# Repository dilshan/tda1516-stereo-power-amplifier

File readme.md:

# TDA1516BQ 12W x 2 Stereo Amplifier

A simple stereo amplifier built around the classic Philips TDA1516BQ audio amplifier chip. It delivers 12W per channel on a 12V - 14V supply, with the warm, smooth sound of a traditional class AB design.

## Features

- Stereo output, 12W x 2
- 12V - 14V supply (tested with a 12V 5A PSU)
- Small PCB: 62mm x 41mm

## Bill of Materials

| Reference | Value | Qty |
|-----------|-------|-----|
| C1 | [100µF / 25V](https://s.click.aliexpress.com/e/_c3xrOqJD) | 1 |
| C2, C3 | [0.22µF](https://s.click.aliexpress.com/e/_c39Y1Dd1) | 2 |
| C4, C5 | [1000µF / 25V](https://s.click.aliexpress.com/e/_c3CeWXvv) | 2 |
| C6 | [2200µF / 25V](https://s.click.aliexpress.com/e/_c3xxjTBN) | 1 |
| C7 | [0.1µF](https://s.click.aliexpress.com/e/_c39Y1Dd1) | 1 |
| J1, J2, J3, J4, J5 | [5.08mm 2-pin screw terminal](https://s.click.aliexpress.com/e/_c3N5smMT) | 5 |
| RV1 | [B100K potentiometer](https://s.click.aliexpress.com/e/_c3qUNW6J) | 1 |
| U1 | [TDA1516BQ](https://s.click.aliexpress.com/e/_c3Xf7b8X) ([datasheet](https://pdf.datasheetcatalog.com/datasheet/philips/TDA1516.pdf)) | 1 |

The PCB can be ordered directly from [PCBWay](https://www.pcbway.com/project/shareproject/TDA1516BQ_12W_x_2_Stereo_Amplifier_b292c3b0.html).

## Construction notes

The build is straightforward. The only thing that needs care is mounting the heatsink. Large capacitors leave little room for tightening the heatsink screws, so use one of these approaches:

1. Solder the TDA1516BQ first, attach the heatsink, then solder the remaining components.
2. Solder all passive components and connectors first, and solder the TDA1516BQ last with the heatsink already attached.

## Power

Use a 12V supply, rated 5A or more. The amplifier works well and produces good quality audio with a 12V 5A PSU.

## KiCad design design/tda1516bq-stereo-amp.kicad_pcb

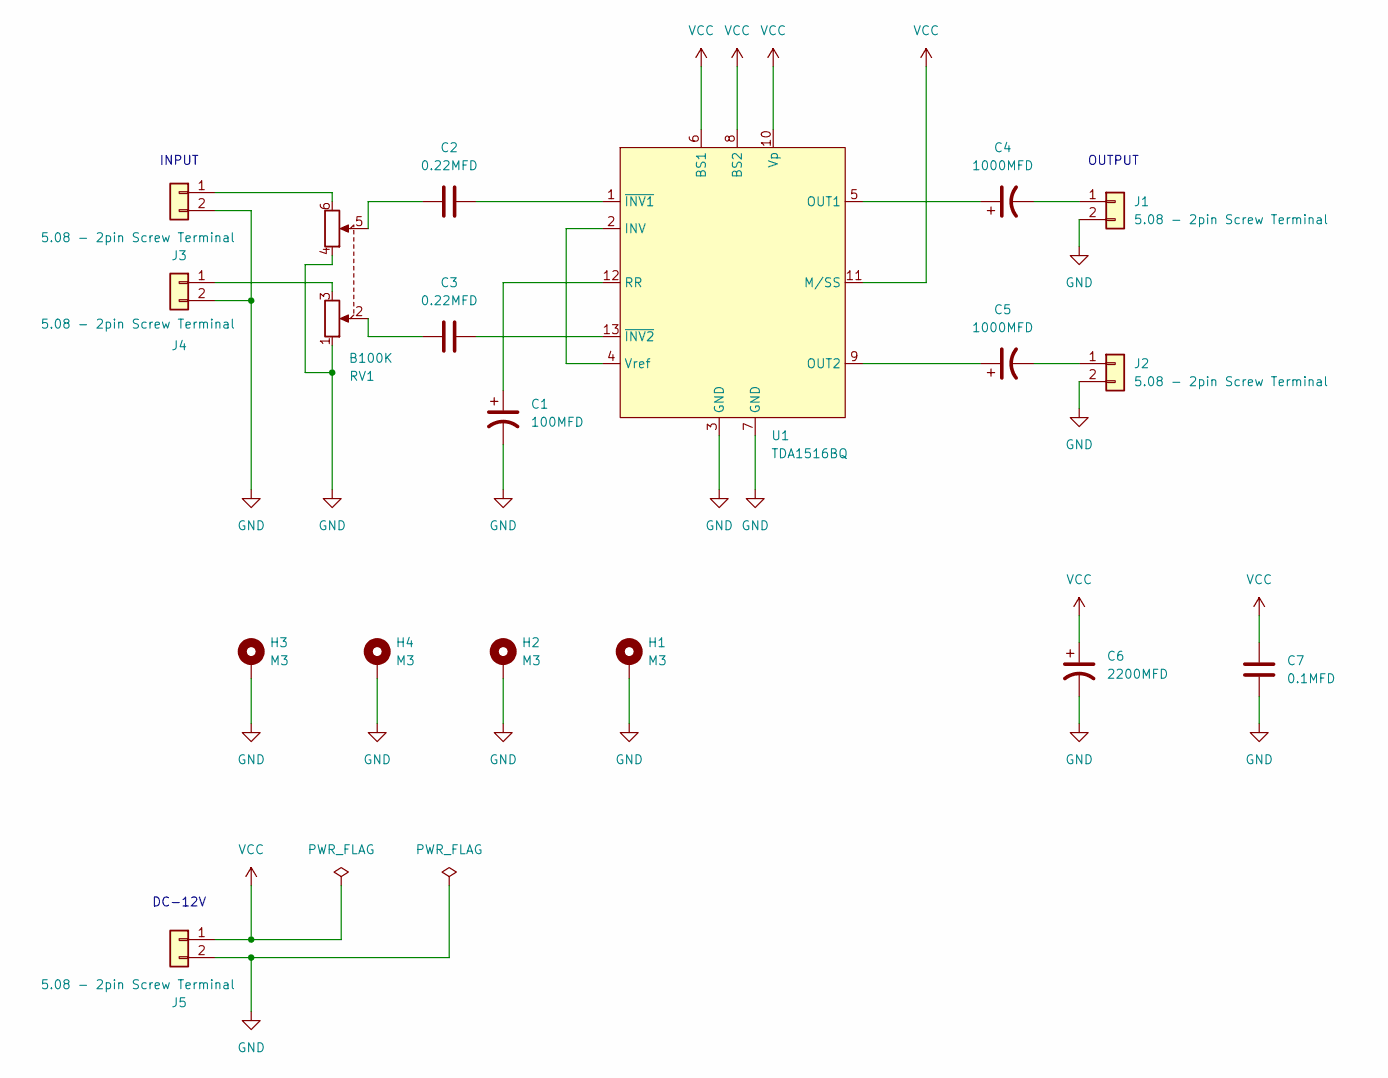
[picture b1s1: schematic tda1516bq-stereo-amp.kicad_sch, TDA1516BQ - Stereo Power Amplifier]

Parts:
C1: 100MFD; CP_Radial_D8.0mm_P3.80mm
C2, C3: 0.22MFD; C_Rect_L11.0mm_W5.1mm_P10.00mm_MKT
C4, C5: 1000MFD; CP_Radial_D12.5mm_P5.00mm
C6: 2200MFD; CP_Radial_D16.0mm_P7.50mm
C7: 0.1MFD; C_Rect_L9.0mm_W4.2mm_P7.50mm_MKT
H1, H2, H3, H4: M3; MountingHole_3.2mm_M3_DIN965_Pad
J1, J2, J3, J4, J5: 5.08 - 2pin Screw Terminal; PhoenixContact_MCV_1,5_2-G-5.08_1x02_P5.08mm_Vertical
RV1: B100K; Potentiometer_Dual
U1: TDA1516BQ; MULTIWAT-SIL13

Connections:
GND: C1.2, C6.2, C7.1, H1.1, H2.1, H3.1, H4.1, J1.2, J2.2, J3.2, J4.2, J5.2, RV1.1, RV1.4, U1.3 (GND), U1.7 (GND)
unnamed: C2.1, RV1.5
unnamed: C3.1, RV1.2
unnamed: C4.2, J1.1
unnamed: C5.2, J2.1
unnamed: J3.1, RV1.6
unnamed: J4.1, RV1.3
unnamed: U1.2 (INV), U1.4 (Vref)
unnamed: C4.1, U1.5 (OUT1)
unnamed: C5.1, U1.9 (OUT2)
unnamed: C1.1, U1.12 (RR)
unnamed: C2.2, U1.1 (~INV1)
unnamed: C3.2, U1.13 (~INV2)
VCC: C6.1, C7.2, J5.1, U1.6 (BS1), U1.8 (BS2), U1.10 (Vp), U1.11 (M/SS)

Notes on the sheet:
INPUT
DC-12V
OUTPUT

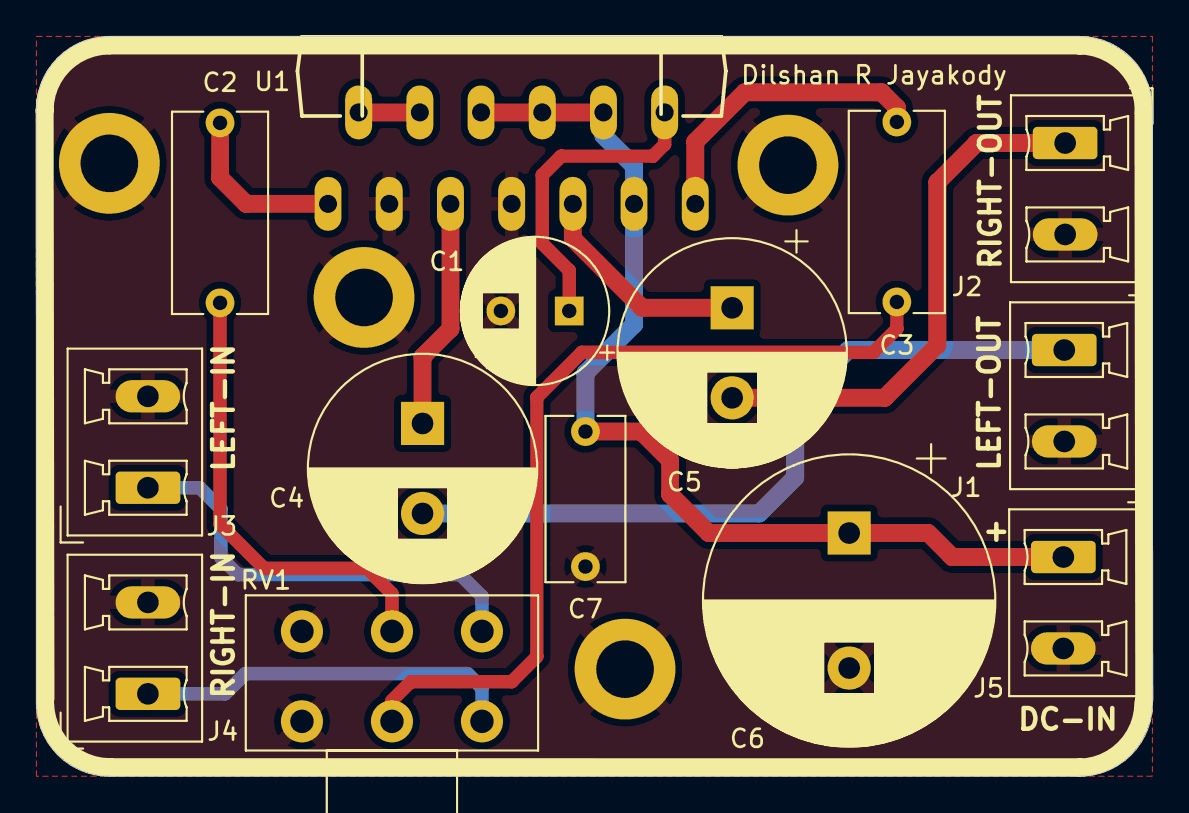
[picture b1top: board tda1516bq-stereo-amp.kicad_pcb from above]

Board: 2 copper layers, 62.0 x 41.1 mm, 18 parts (0 on the bottom side), 14 nets.

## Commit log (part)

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2025-03-18 Add initial version of design files.
